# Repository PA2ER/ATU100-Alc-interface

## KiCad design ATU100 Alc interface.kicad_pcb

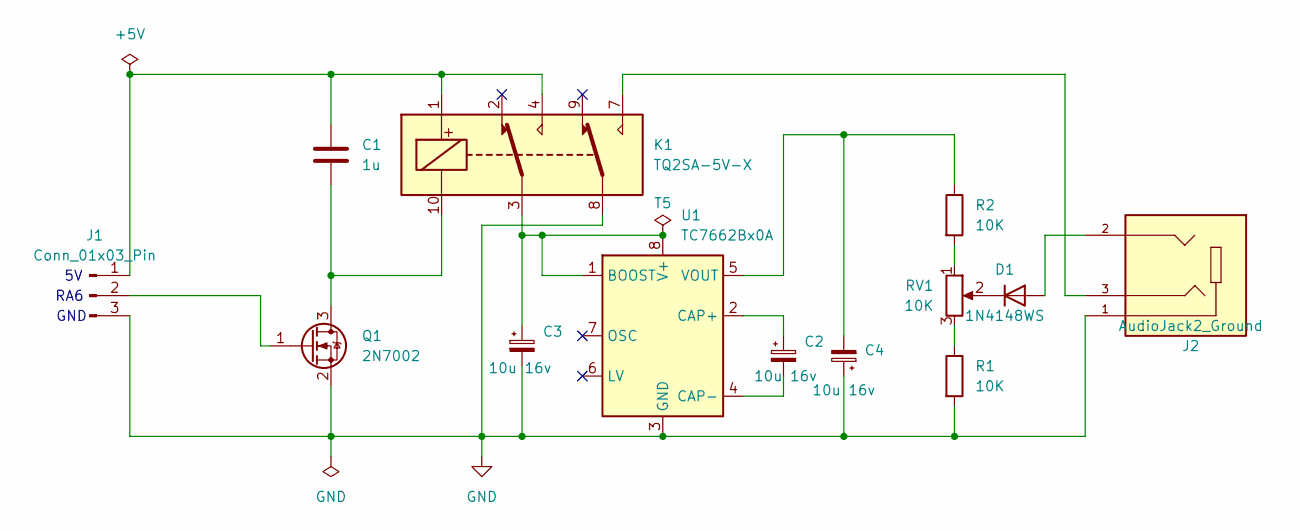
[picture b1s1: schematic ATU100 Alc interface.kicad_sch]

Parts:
C1: 1u; C_0805_2012Metric_Pad1.18x1.45mm_HandSolder
C2, C3, C4: 10u 16v; CP_EIA-3216-10_Kemet-I_Pad1.58x1.35mm_HandSolder
D1: 1N4148WS; D_SOD-323
J1: Conn_01x03_Pin; PinHeader_1x03_P1.27mm_Vertical
J2: AudioJack2_Ground; CUI_SJ1-3523N; PARTREV 1.05
K1: TQ2SA-5V-X; Relay_DPDT_FRT5_SMD
Q1: 2N7002; SOT-23
R1, R2: 10K; R_0805_2012Metric_Pad1.20x1.40mm_HandSolder
RV1: 10K; Potentiometer_Bourns_3006P_Horizontal
U1: TC7662Bx0A; SOIC-8_3.9x4.9mm_P1.27mm

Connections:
GND: C3.2, C4.1, J1.3, J2.1, K1.8, Q1.2 (S), R1.2, U1.3 (GND)
unnamed: D1.2 (A), J2.2
unnamed: D1.1 (K), RV1.2
unnamed: C1.1, J1.1, K1.1, K1.4
unnamed: J1.2, Q1.1 (G)
unnamed: J2.3, K1.7
unnamed: C1.2, K1.10, Q1.3 (D)
unnamed: R1.1, RV1.3
unnamed: R2.2, RV1.1
unnamed: C3.1, K1.3, U1.1 (BOOST), U1.8 (V+)
unnamed: C2.1, U1.2 (CAP+)
unnamed: C2.2, U1.4 (CAP-)
unnamed: C4.2, R2.1, U1.5 (VOUT)

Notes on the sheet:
GND
RA6

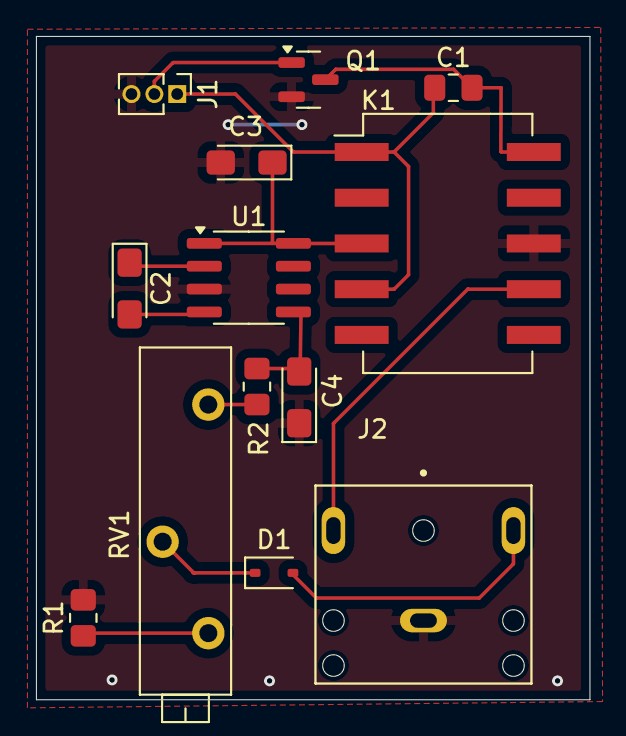
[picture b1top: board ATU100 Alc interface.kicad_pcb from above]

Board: 2 copper layers, 30.8 x 36.9 mm, 13 parts (0 on the bottom side), 13 nets.

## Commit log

2024-09-29 29-09-2024
    Error holse corrected
2024-09-29 29-09-2024 geber updated
    29-09-2024 geber updated
2024-09-29 29-09-2024
2024-10-10 10-10-2024
